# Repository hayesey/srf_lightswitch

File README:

srf_lightswitch
-----
Originally written sometime in 2015
2016-11-17 put on github
2016-11-21 added filter info
-----

This is my home-made "IoT" light switch.  The idea is that you can retrofit this into a lamp or ceiling light to turn the light on and off remotely.  In addition you can connect up the existing bistable switch (i.e. the light switch) to also operate the light in order to maintain the operation people expect of a light & light switch.

It's based on a Texas Instruments CC1110 System-on-Chip.  The module I use is actually an SRF module from the sadly now defunct Ciseco/Wireless Things company.  This and all other components are mounted to a PCB of my own design.

It uses a PCB mounted mains voltage transformer, this actually powers the microcontroller and other parts of the circuit from the mains voltage going to the light itself.  No batteries are needed or any other means of power.

Files:

'SRF Light Switch' folder contains the design, layout and gerber files for the PCB.  The software I use is Cadsoft Eagle.  I used Seeedstudio Fusion PCB online service for the production of prototype boards.  They are very cheap but since the work is done in China, delivery takes weeks.

'Firmware' folder contains the C code for the CC1110 chip to make the light switch work.  I would definitely call it a prototype, it is probably full of bugs.  It has some basic LLAP commands to control the light switch from other devices such as Ciseco XRF modules.

To use this you'll need the Small Devices C Compiler (sdcc) and some way burning the compiled firmware on to the CC1110 device.  I use a proper TI CC-Debugger, they are under £40.  I believe a Raspberry Pi can also be used to bit-bang it.  See this:

http://paulswasteland.blogspot.co.uk/2015/01/building-your-own-firmware-for-ciseco.html

Use at your own risk anyone who finds this.  I only ever intended this to be for experimentation or fun.

Note - there was an error by me with the PCB layout that didn't come to light until after I had them produced.  This is that I hadn't included the low pass filter on the output of the 3.3v transformer.  Without this the radio performance is very poor.  I made a small veroboard circuit to add the filter, there is an eagle schematic and layout showing this and the parts are included in the BOM.  Values are from the datasheet for the Vigortronix transformer.

Paul Hayes.

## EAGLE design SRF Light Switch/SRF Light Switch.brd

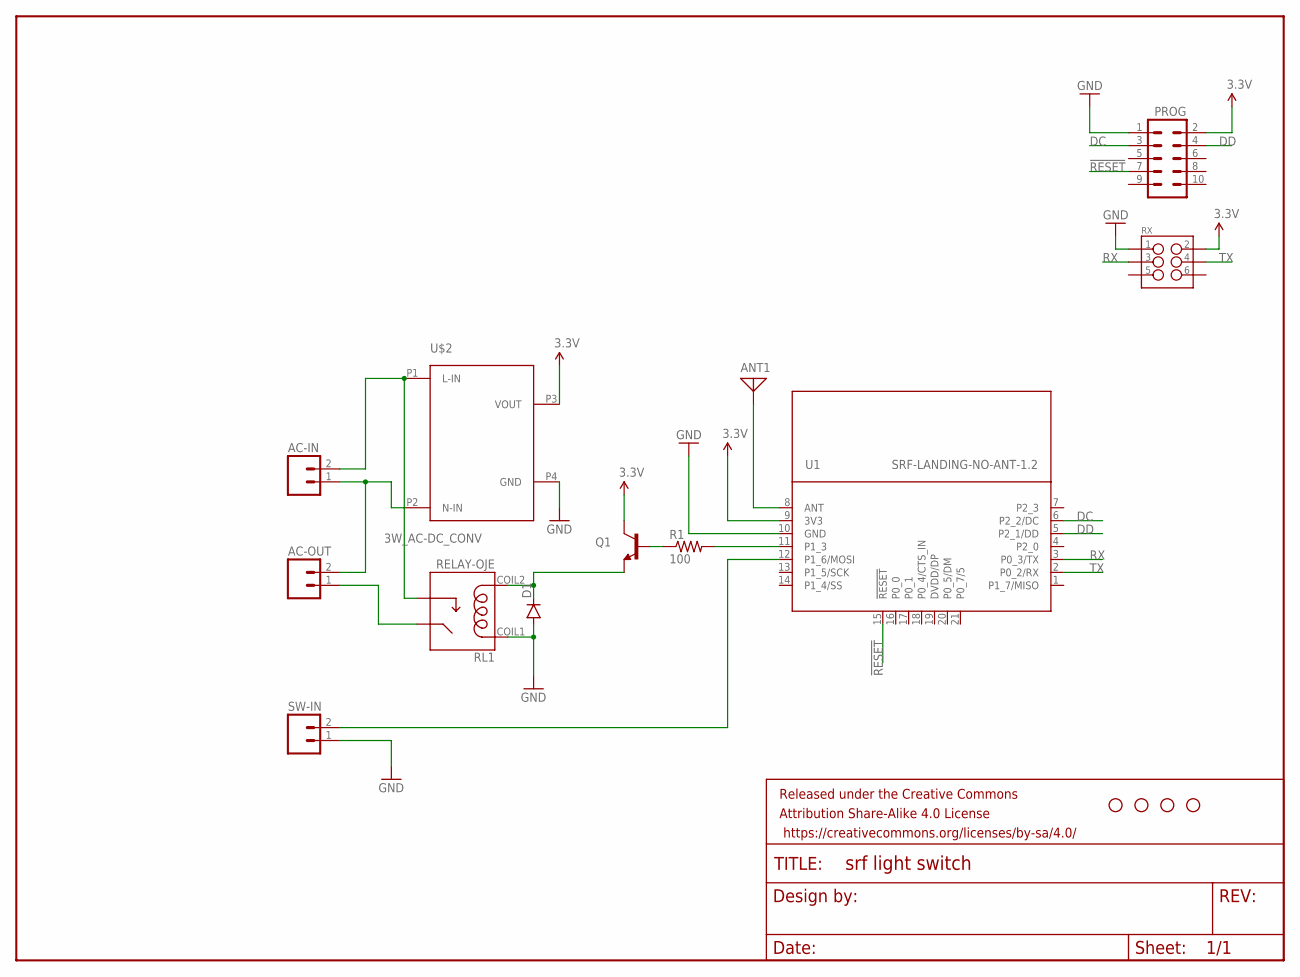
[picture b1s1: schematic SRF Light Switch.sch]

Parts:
AC-IN: M025MM; SCREWTERMINAL-5MM-2
AC-OUT: M025MM; SCREWTERMINAL-5MM-2
ANT1: ANTENNA; PAD-01
D1: DIODEPTH; DIODE-1N4001
FRAME1: FRAME-LETTER; CREATIVE_COMMONS
PROG: M05X2SHD; 2X5-SHROUDED
Q1: TRANSISTOR_NPNTO92; TO-92
R1: 100; AXIAL-0.4
RL1: RELAY-OJE
RX: M03X2SHROUD; 2X3-SHROUDED
STANDOFF1, STANDOFF2, STANDOFF3, STANDOFF4: STAND-OFF
SW-IN: M025MM; SCREWTERMINAL-5MM-2
U1: SRF-LANDING-NO-ANT-1.2
U$2: 3W_AC-DC_CONV

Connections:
3.3V: PROG.2, Q1.3 (C), RX.2, U1.9 (3V3), U$2.P3 (VOUT)
!RESET: PROG.7, U1.15 (!RESET)
ANT: ANT1.1, U1.8 (ANT)
DC: PROG.3, U1.6 (P2_2/DC)
DD: PROG.4, U1.5 (P2_1/DD)
GND: D1.A, PROG.1, RL1.COIL1, RX.1, SW-IN.1, U1.10 (GND), U$2.P4 (GND)
unnamed: D1.C, Q1.1 (E), RL1.COIL2
unnamed: AC-IN.2, RL1.NO, U$2.P1 (L-IN)
unnamed: SW-IN.2, U1.12 (P1_6/MOSI)
unnamed: Q1.2 (B), R1.P$1 (1)
unnamed: R1.P$2 (2), U1.11 (P1_3)
unnamed: AC-IN.1, AC-OUT.2, U$2.P2 (N-IN)
unnamed: AC-OUT.1, RL1.COM
RX: RX.3, U1.3 (P0_3/TX)
TX: RX.4, U1.2 (P0_2/RX)

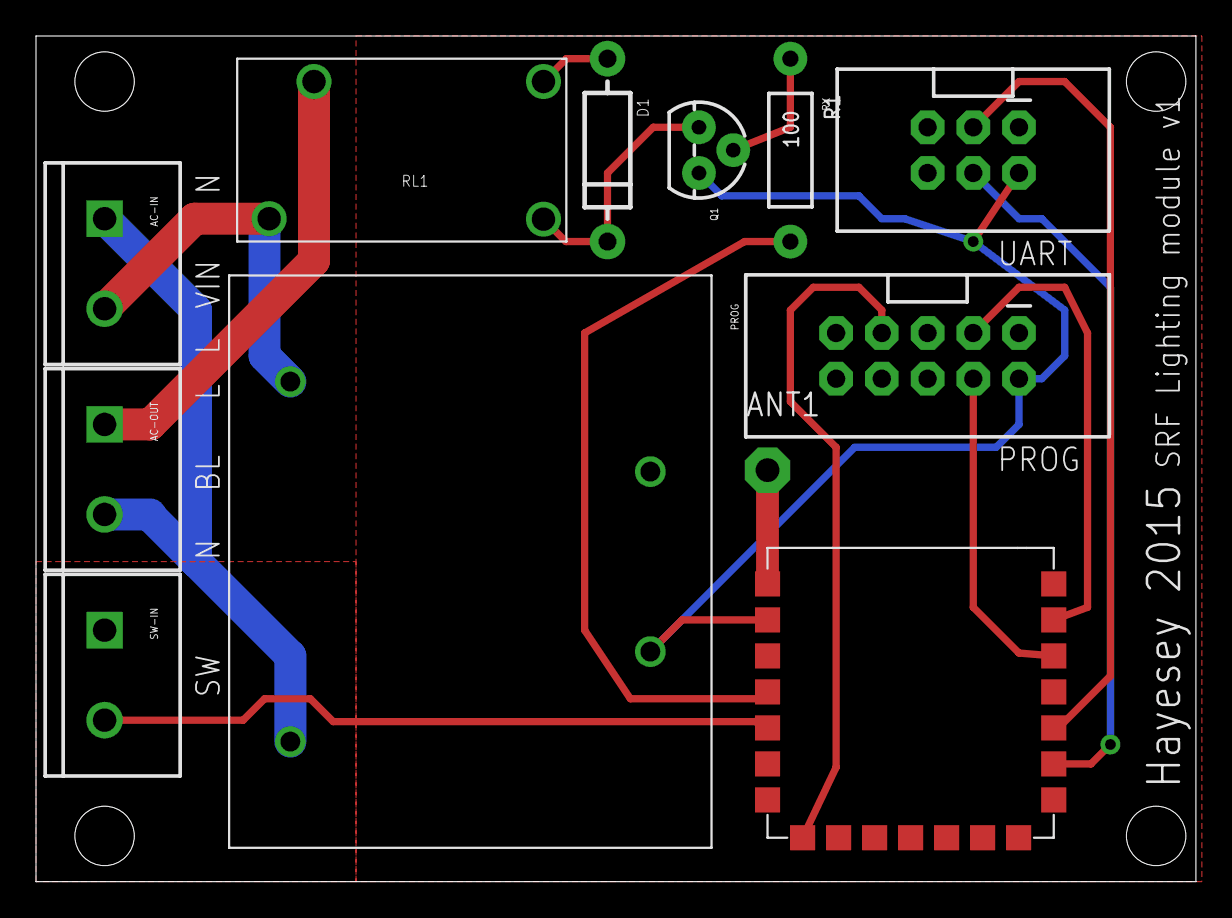
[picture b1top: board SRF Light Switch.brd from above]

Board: 2 copper layers, 64.4 x 47.0 mm, 17 parts (0 on the bottom side), 15 nets.

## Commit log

2016-11-17 adding to github
2016-11-17 readme
2016-11-17 remove some files
2016-11-21 added filter veroboard eagle layout
2016-11-21 info about filter add-on board
2016-12-30 changes to keep llap id in a variable not working yet
2017-01-05 added uploader to makefile
2017-01-05 llap ID stored in single variable
2017-01-05 gitignore and get rid of build files
2017-11-21 1.2k
2017-11-23 rewrite of radio register settings, matches smartrf now
2017-11-23 added registers spreadsheet

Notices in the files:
parts and their libraries:
SparkFun-DiscreteSemi: Licensing: Creative Commons ShareAlike 4.0 International - https://creativecommons.org/licenses/by-sa/4.0
SparkFun-Aesthetics: Released under the Creative Commons Attribution Share-Alike 4.0 License
SparkFun-Aesthetics: https://creativecommons.org/licenses/by-sa/4.0
